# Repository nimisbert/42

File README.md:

# 42

## Summary 

Answers to the questions of my universe and anything...  
Well, my global aim is to create an unified dynamic system modeling program in Haskell.  
There are also other topics, like cryptography and electronics hardware, that I may develop along the way to this so called unified dynamic systems modeler.

## Folders 

| folder       | description            |
|:------------:|:-----------------------|
| [HW](./HW)   | Hardware development   |
| [SW](./SW)   | Software development   |

## Books

-  Loudon Kyle, _Mastering algorithm with C_, __O'REILLY__, April 2002 
-  Mecklenburg Robert, _Managing Projects with GNU Make_, __O'REILLY__, November 2004
-  Lipovača Miran, _Learn You a Haskell for Great Good!_, __No Starch Press__, 2011
-  B. Mark, _64-bit assembly programming for Linux_, __Sharanych Media__, 2020
-  P. Horowitz & W. Hill, _The Art of Electronics_, __Cambridge University Press__, 2015
-  S. Dusausay, _L'Electronique par la simulation_, 2023
-  Jon B. Hagen, _Radio Frequency Electronics_, __Cambridge University Press__, 2009

## Projects

-  Cryptography Algorithms in C
-  Biologic dynamic systems modeler in Haskell
-  Electronic circuits modeler in C
-  Unified systems modeler in Haskell

## Roadmap

```mermaid
flowchart TB
classDef blue fill:#2374f7,stroke:#000,stroke-width:2px,color:#fff
classDef orange fill:#fc822b,stroke:#000,stroke-width:2px,color:#fff

B1(The art of electronics):::blue 
B2(Electronique par la simulation):::blue
B3(Radio frequency electronics):::blue
B4(Mastering algorithm with C):::blue
B5(CGP Math):::blue
B6(Learn you a Haskell for great good!):::blue

O1(LTspice reference simulations):::orange
O2(C based circuits modeler):::orange
O3(Biologic dynamic systems modeler):::orange
O4(Unified dynamic system modeler in Haskell):::orange
O5(Cryptography in C):::orange

B1 ---> B2 & O1
B2 ---> B3 & O1
B3 ---> O1
O1 ---> O2
B3 ---> O2
B4 ---> O2
B5 ---> O3
B6 ---> O3
O3 ---> O4
O2 ---> O4
B4 ---> O5
```

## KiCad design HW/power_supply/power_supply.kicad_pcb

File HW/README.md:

# Hardware (HW)

The HW folder contains electronic Hardware schematics and routings, using Kicad. Some simulations with LTspice as well.

| folder                             | description                                                     |
|:----------------------------------:|:----------------------------------------------------------------|
| [simulations](./HW/simulations/)   | electrical simulations with LTspice                             |

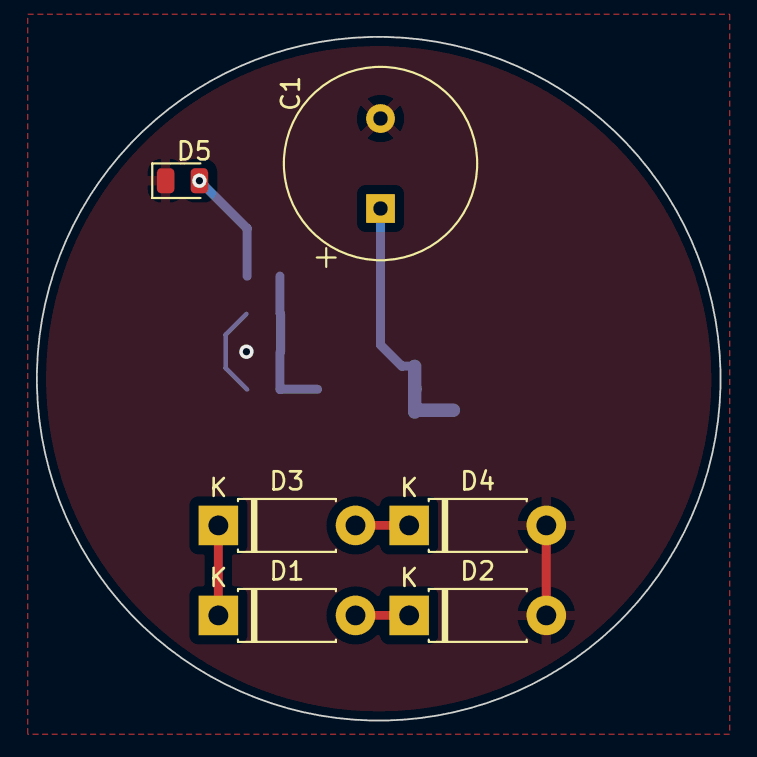
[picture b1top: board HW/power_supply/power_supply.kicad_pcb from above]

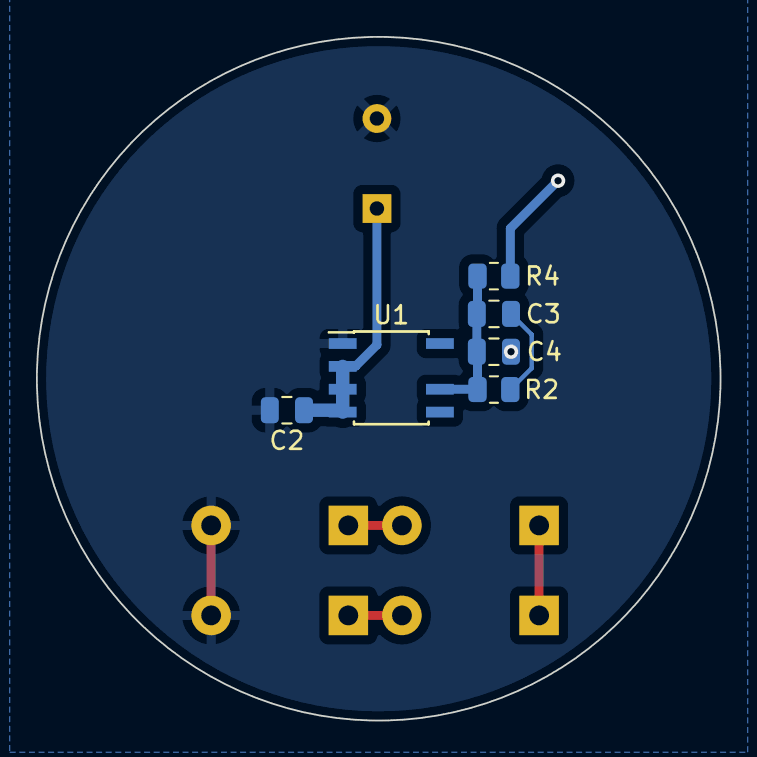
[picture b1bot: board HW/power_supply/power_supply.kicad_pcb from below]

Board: 2 copper layers, 38.0 x 38.0 mm, 12 parts (6 on the bottom side), 8 nets.

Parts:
C1: 470u; CP_Radial_Tantal_D10.5mm_P5.00mm
C2, C4: 1u; C_0805_2012Metric
C3: 68p; C_0805_2012Metric
D1, D2, D3, D4: 1N4007RLG; D_DO-41_SOD81_P7.62mm_Horizontal
D5: LED; D_0805_2012Metric
R2: 1k; R_0805_2012Metric
R4: 220; R_0805_2012Metric
U1: NCP3334; SOIC-8-N7_3.9x4.9mm_P1.27mm

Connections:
MIN: D3.2 (A), D4.1 (K)
NEUTRE: C1.2, C2.2, C4.2, D2.2 (A), D4.2 (A), D5.1 (K), U1.1 (GND)
unnamed: C3.2, R2.1
unnamed: D5.2 (A), R4.1
POS: D1.2 (A), D2.1 (K)
REGIN: C1.1, C2.1, U1.2 (~SD), U1.3 (IN), U1.4 (IN)
REGOUT: C3.1, C4.1, R2.2, R4.2, U1.5 (OUT), U1.6 (OUT)
VIN: D1.1 (K), D3.1 (K)

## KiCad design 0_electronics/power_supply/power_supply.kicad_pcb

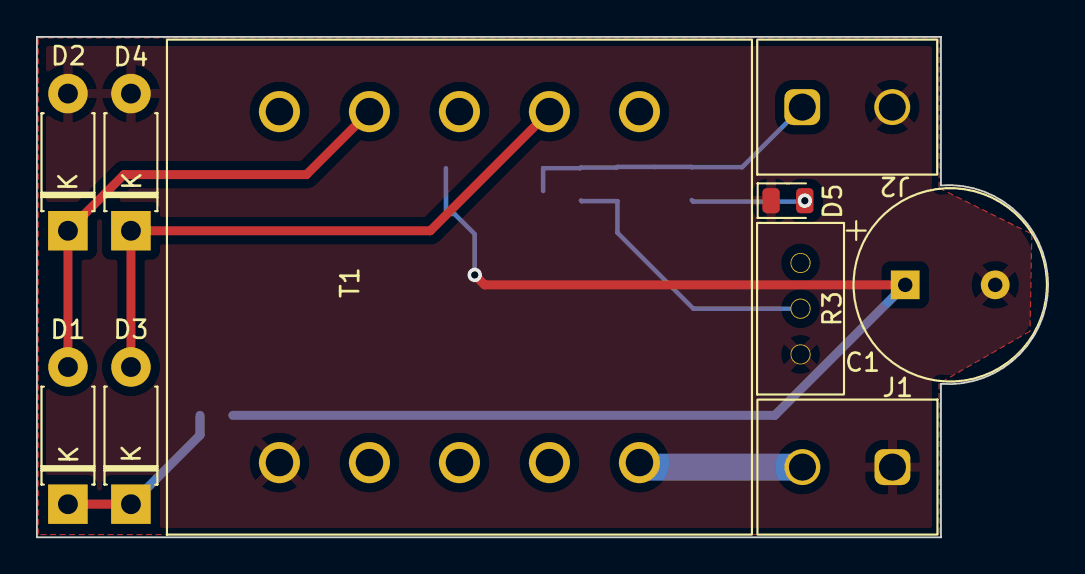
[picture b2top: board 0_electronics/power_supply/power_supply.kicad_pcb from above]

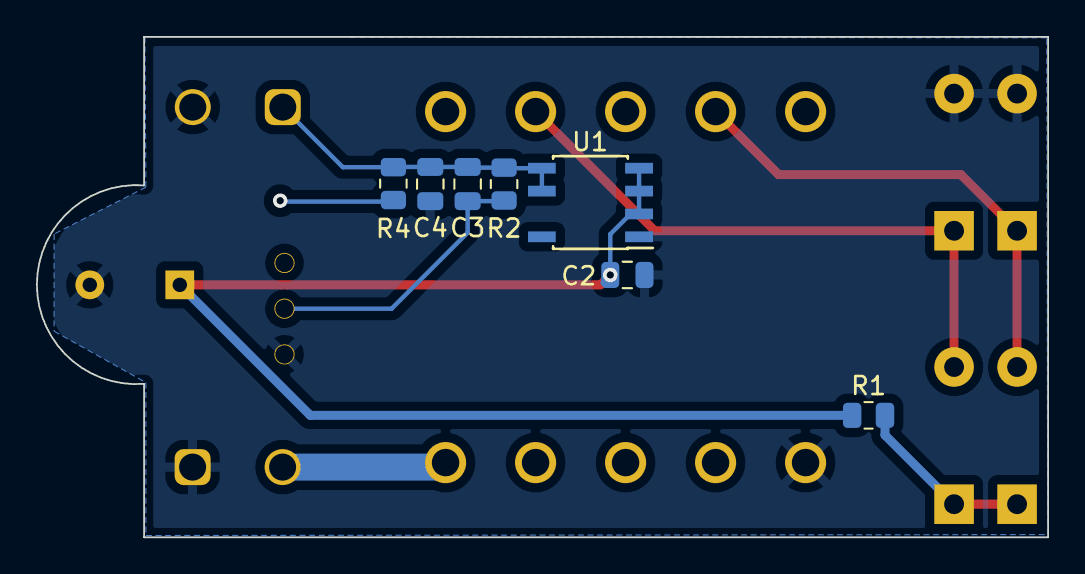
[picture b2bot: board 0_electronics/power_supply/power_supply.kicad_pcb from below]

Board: 2 copper layers, 56.2 x 27.8 mm, 17 parts (7 on the bottom side), 9 nets.

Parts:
C1: 470u; CP_Radial_Tantal_D10.5mm_P5.00mm
C2, C4: 1u; C_0805_2012Metric
C3: 68p; C_0805_2012Metric
D1, D2, D3, D4: 1N4007RLG; D_DO-41_SOD81_P7.62mm_Horizontal
D5: LED; D_0805_2012Metric
J1: INPUT; bornier_1x2_p5.00mm
J2: OUTPUT; bornier_1x2_p5.00mm
R1: 130; R_0805_2012Metric
R2: 1k; R_0805_2012Metric
R3: 100-1k; 3296W-1-102LF
R4: 220; R_0805_2012Metric
T1: RSPRO_121-3824; RSRO_121-3824
U1: NCP3334; SOIC-8-N7_3.9x4.9mm_P1.27mm

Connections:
MIN: D3.2 (A), D4.1 (K), T1.9 (SA)
NEUTRE: C1.2, C2.2, C4.2, D2.2 (A), D4.2 (A), D5.1 (K), J1.1, J2.2, R3.1, T1.5 (AB), U1.1 (GND)
unnamed: C3.2, R2.1, R3.2
unnamed: D5.2 (A), R4.1
PHASE: J1.2, T1.1 (AA)
POS: D1.2 (A), D2.1 (K), T1.7
REGIN: C1.1, C2.1, R1.1, U1.2 (~SD), U1.3 (IN), U1.4 (IN)
REGOUT: C3.1, C4.1, J2.1, R2.2, R4.2, U1.5 (OUT), U1.6 (OUT)
VIN: D1.1 (K), D3.1 (K), R1.2

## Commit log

2022-07-09 readme
2022-07-09 hidden license & readme
2022-07-09 work so far
2022-07-09 cleanup
2022-07-09 spiegel section 4 up to page 7, ellipse + integral by composite trapezoidal rule
2022-07-09 small changes to readme
2022-07-09 forgot some spacing
2022-07-09 still not the best .md
2022-07-09 whatever
2022-07-10 starting volumes
2022-07-10 code section 4 done but uncommented
2022-07-11 begin work on section 5
2022-07-12 spiegel section 5, not commented
2022-07-13 section 6, complex numbers
2022-07-14 better .md, removed spiegel6 because complex.h working on spiegel9
2022-07-14 added quadratic equation solver
2022-07-16 begin spiegel 10
2022-08-21 added RII & RIF
2022-09-08 book about algos
2022-09-08 some changes
2022-09-08 some other changes
2022-09-08 modify to create conflicts
2022-09-08 some modifs for conflicts
2022-09-22 holydays catchup
2022-09-22 changed readme
2022-09-22 changed readme yet again
2022-09-24 power supply schematics
2022-09-25 power supply pcb begin
2022-09-25 RC low pass design for power_supply
2022-10-08 power supply done, to check
2022-10-09 double linked list
2022-10-23 chapter2 atom
2022-10-30 list rework
2022-10-30 added some openscad project
2022-11-11 rework
2022-11-11 removed some stuff after rework
2022-11-11 rework sll
2022-11-11 removed zip files from power_supply
2022-11-11 list insert next
2022-11-12 insert next logic corrected
2023-02-12 reworking again
2023-02-13 singly linked list begin
2023-02-27 finding bearings
2023-02-27 correction sll.h et sll.c
2023-02-27 clean SW
2023-03-04 clean Makefile and README
2023-03-04 singly linked list ok + frames exemple
2023-03-05 doubly linked list TODO test
2023-03-11 switched to cmake
2023-03-11 cleanup build
2023-03-12 chapitre sur les piles (stack)
2023-03-12 queue
2023-03-14 begin set
2023-03-16 set cover function, minor changes, author header
2023-03-16 modified(?) gitignore
2023-03-19 fixed kset bugs, forgot return and free on & of a pointer...
2023-03-19 fixed problem statement
2023-03-20 bug sll.c line 78 caused unexpected behavior of set_cover (fixed), Set cover example done
2023-03-21 begin hash tables
2023-03-24 added chtbl.c content
2023-03-26 starting haskell journey
2023-03-26 lists exercices begin
2023-03-26 rework a bad readme into a weird one
2023-03-27 list exe + higher order functions
2023-03-28 folding.hs exercices
2023-03-29 starting D3
2023-03-30 chagement de sources pour les exos en haskell
2023-03-30 sol lewit D3
2023-03-30 Update README.md
    funnier Readme
2023-04-08 removed unrelevant
2023-04-16 starting binary tree & haskell mini project
2023-04-22 begin work on cryptography
2023-04-22 better readme
2023-04-22 added scytale
2023-04-23 AES to debug
2023-04-24 AES 128 and FIPS-197 appendix B examples
2023-04-25 AES test 197 FIPS appendix-A .1 .2 & .3
2023-04-25 fixed some stuff
2023-04-27 added AES appendix C.1 .2 .3
2023-04-27 begin vigenere
2023-04-29 vigenere
2023-04-30 some name changes
2023-04-30 updated some readmes
2023-05-03 memo for haskell book because my brain hurts
2023-05-13 done some haskell
2023-05-14 graph with Haskell-Chart
2023-05-18 switched to Project Euler to improve skills
2023-05-27 reworked learning haskell
2023-05-28 algebra exe 2.3
2023-05-29 algebra exercice 3.1
2023-06-01 haskell algebra and graphs
2023-06-10 haskell exe42
2023-06-15 quadratics and cubics start
2023-06-17 better quadratics and cubics + exe11
2023-06-18 q&c exe12 + modelling fundamentals
2023-06-19 added Runge-Kutta for task 4.4 of Modelling
2023-06-19 modified ignore
2023-06-20 logistic equation analytic and runge-kutta
2023-06-21 added schaefer
2023-06-24 plot task41 with Haskell Charts
2023-06-25 omit plots folder
2023-06-25 switch to Haskell-Charts for plots
2023-06-26 radio + models fund in Chart
2023-06-26 Power transfer
2023-06-27 added .raw .log .DS_Store
2023-06-27 basic ltspice simus
2023-06-28 article 44
2023-06-30 simulations readme
2023-07-01 first go at a battery charged by a PV panel
2023-07-01 RCRC & Colpitts
2023-07-02 LM308 inverter
2023-07-04 D logic gate
2023-07-06 Center tapped full-wave rectifier & Dual polarity split supply
2023-07-07 READMEs & Ladder solver begin
2023-07-08 Diode sig rectifier & ladder solver in C & LTspice ref solver
2023-07-09 cleanup & better pvcell
2023-07-11 deleted old hardware & modified READMEs
2023-07-14 plot in Gloss
2023-07-15 gloss plots v2
2023-08-03 readme link problem and CGP quadratics and cubics 1.3
